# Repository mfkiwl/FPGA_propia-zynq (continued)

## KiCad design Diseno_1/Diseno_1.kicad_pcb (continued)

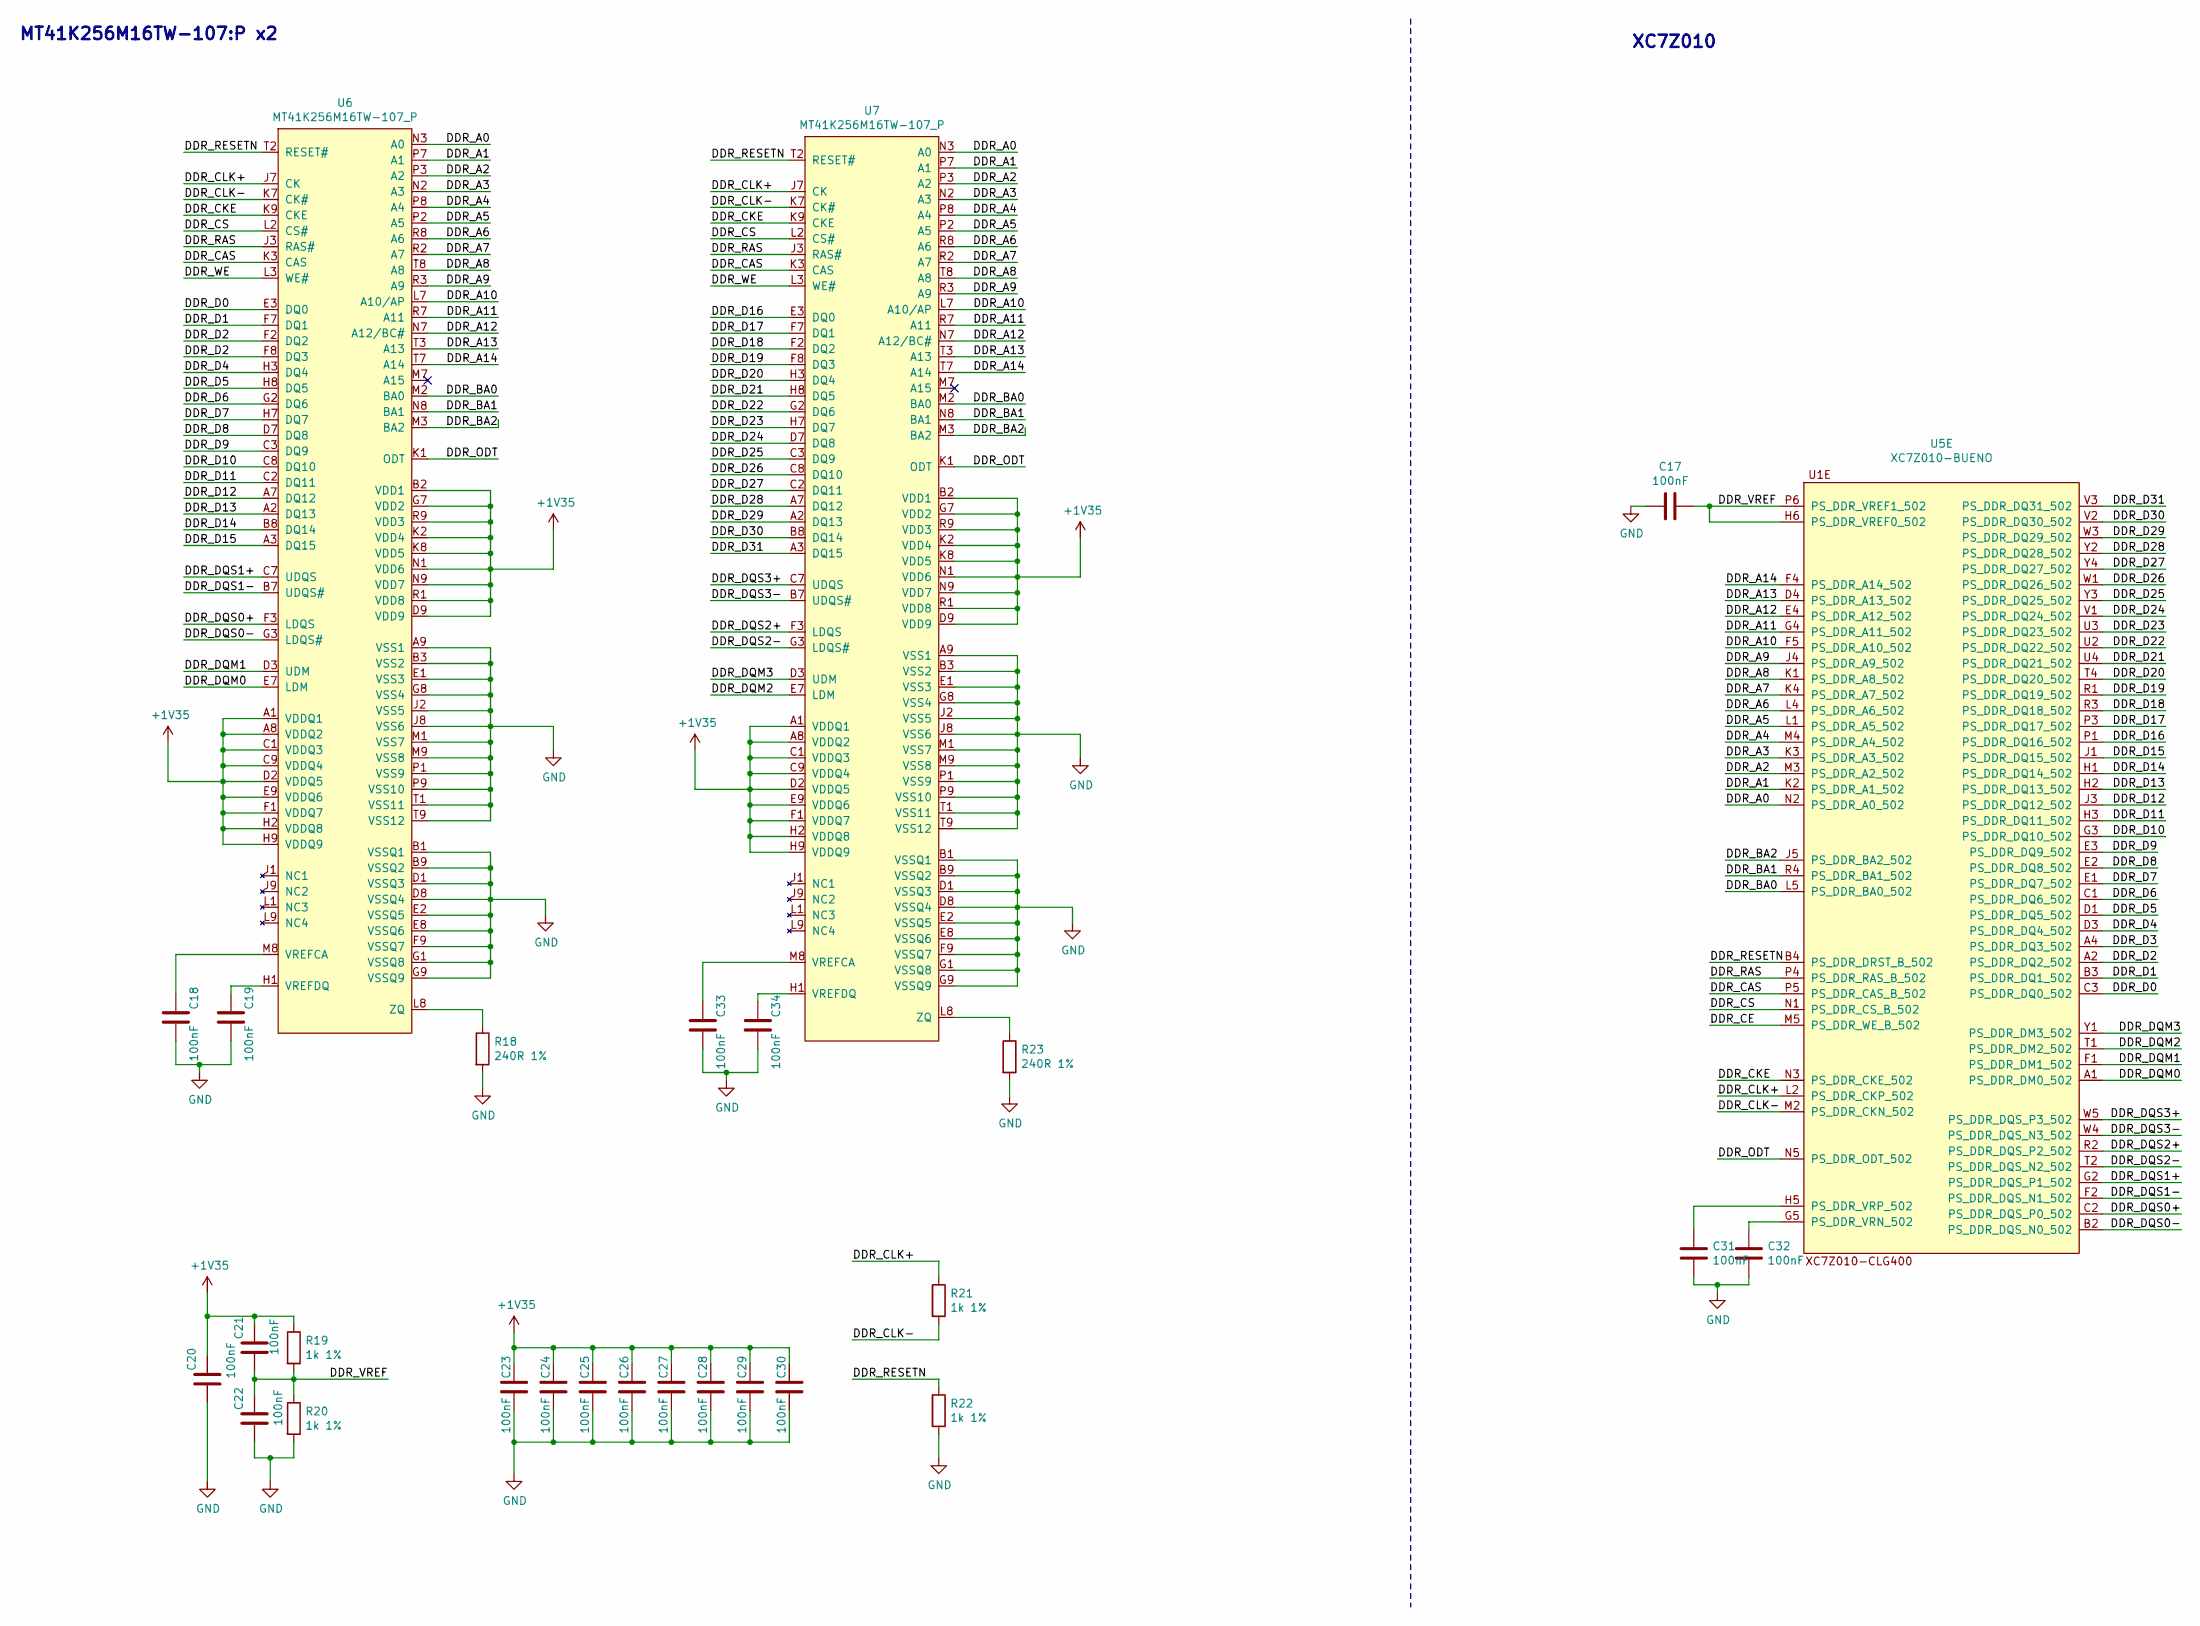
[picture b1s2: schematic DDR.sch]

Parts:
C17, C18, C19, C20, C21, C22, C23, C24, C25, C26, C27, C28, C29, C30, C31, C32, C33, C34: 100nF; C_0805_2012Metric
R18, R23: 240R 1%; R_0805_2012Metric
R19, R20, R21, R22: 1k 1%; R_0805_2012Metric
U5: XC7Z010-BUENO; BGA-400_20x20_17.0x17.0mm
U6, U7: MT41K256M16TW-107_P; BGA-144_9x16_8.0x14.0mm

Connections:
+1V35: C20.1, C21.1, C23.1, C24.1, C25.1, C26.1, C27.1, C28.1, C29.1, C30.1, R19.1, U6.A1 (VDDQ1), U6.A8 (VDDQ2), U6.B2 (VDD1), U6.C1 (VDDQ3), U6.C9 (VDDQ4), U6.D2 (VDDQ5), U6.D9 (VDD9), U6.E9 (VDDQ6), U6.F1 (VDDQ7), U6.G7 (VDD2), U6.H2 (VDDQ8), U6.H9 (VDDQ9), U6.K2 (VDD4), U6.K8 (VDD5), U6.N1 (VDD6), U6.N9 (VDD7), U6.R1 (VDD8), U6.R9 (VDD3), U7.A1 (VDDQ1), U7.A8 (VDDQ2), U7.B2 (VDD1), U7.C1 (VDDQ3), U7.C9 (VDDQ4), U7.D2 (VDDQ5), U7.D9 (VDD9), U7.E9 (VDDQ6), U7.F1 (VDDQ7), U7.G7 (VDD2), U7.H2 (VDDQ8), U7.H9 (VDDQ9), U7.K2 (VDD4), U7.K8 (VDD5), U7.N1 (VDD6), U7.N9 (VDD7), U7.R1 (VDD8), U7.R9 (VDD3); also elsewhere on the board
/Entradas y Salidas/BANK34_N17: U5.N17 (IO_L23P_T3_34); also elsewhere on the board
/Entradas y Salidas/BANK34_N18: U5.N18 (IO_L13P_T2_MRCC_34); also elsewhere on the board
/Entradas y Salidas/BANK34_N20: U5.N20 (IO_L14P_T2_SRCC_34); also elsewhere on the board
/Entradas y Salidas/BANK34_P14: U5.P14 (IO_L6P_T0_34); also elsewhere on the board
/Entradas y Salidas/BANK34_P15: U5.P15 (IO_L24P_T3_34); also elsewhere on the board
/Entradas y Salidas/BANK34_P16: U5.P16 (IO_L24N_T3_34); also elsewhere on the board
/Entradas y Salidas/BANK34_P18: U5.P18 (IO_L23N_T3_34); also elsewhere on the board
/Entradas y Salidas/BANK34_P19: U5.P19 (IO_L13N_T2_MRCC_34); also elsewhere on the board
/Entradas y Salidas/BANK34_P20: U5.P20 (IO_L14N_T2_SRCC_34); also elsewhere on the board
/Entradas y Salidas/BANK34_R14: U5.R14 (IO_L6N_T0_VREF_34); also elsewhere on the board
/Entradas y Salidas/BANK34_R16: U5.R16 (IO_L19P_T3_34); also elsewhere on the board
/Entradas y Salidas/BANK34_R17: U5.R17 (IO_L19N_T3_VREF_34); also elsewhere on the board
/Entradas y Salidas/BANK34_R18: U5.R18 (IO_L20N_T3_34); also elsewhere on the board
/Entradas y Salidas/BANK34_R19: U5.R19 (IO_0_34); also elsewhere on the board
/Entradas y Salidas/BANK34_T10: U5.T10 (IO_L1N_0_34); also elsewhere on the board
/Entradas y Salidas/BANK34_T11: U5.T11 (IO_L1P_T0_34); also elsewhere on the board
/Entradas y Salidas/BANK34_T12: U5.T12 (IO_L2P_T0_34); also elsewhere on the board
/Entradas y Salidas/BANK34_T14: U5.T14 (IO_l5P_T0_34); also elsewhere on the board
/Entradas y Salidas/BANK34_T15: U5.T15 (IO_L5N_T0_34); also elsewhere on the board
/Entradas y Salidas/BANK34_T16: U5.T16 (IO_L9P_T1_DQS_34); also elsewhere on the board
/Entradas y Salidas/BANK34_T17: U5.T17 (IO_L20P_T3_34); also elsewhere on the board
/Entradas y Salidas/BANK34_T19: U5.T19 (IO_25_34); also elsewhere on the board
/Entradas y Salidas/BANK34_T20: U5.T20 (IO_L15P_T2_DQS_34); also elsewhere on the board
/Entradas y Salidas/BANK34_U12: U5.U12 (IO_L2N_T0_34); also elsewhere on the board
/Entradas y Salidas/BANK34_U14: U5.U14 (IO_L11P_T1_SRCC_34); also elsewhere on the board
/Entradas y Salidas/BANK34_U15: U5.U15 (IO_L11N_T1_SRCC_34); also elsewhere on the board
/Entradas y Salidas/BANK34_U17: U5.U17 (IO_L9N_T1_DQS_34); also elsewhere on the board
/Entradas y Salidas/BANK34_U18: U5.U18 (IO_L12P_T1_MRCC_34); also elsewhere on the board
/Entradas y Salidas/BANK34_U19: U5.U19 (IO_L12N_T1_MRCC_34); also elsewhere on the board
/Entradas y Salidas/BANK34_U20: U5.U20 (IO_L5N_T2_DQS_34); also elsewhere on the board
/Entradas y Salidas/BANK34_V12: U5.V12 (IO_L4P_T0_34); also elsewhere on the board
/Entradas y Salidas/BANK34_V13: U5.V13 (IO_L3N_T0_DQS_34); also elsewhere on the board
/Entradas y Salidas/BANK34_V15: U5.V15 (IO_L10P_T1_34); also elsewhere on the board
/Entradas y Salidas/BANK34_V16: U5.V16 (IO_L18P_T2_34); also elsewhere on the board
/Entradas y Salidas/BANK34_V17: U5.V17 (IO_L21P_T3_VREF_34); also elsewhere on the board
/Entradas y Salidas/BANK34_V18: U5.V18 (IO_L21N_T3_DQS_34); also elsewhere on the board
/Entradas y Salidas/BANK34_V20: U5.V20 (IO_L6P_T2_34); also elsewhere on the board
/Entradas y Salidas/BANK34_W13: U5.W13 (IO_L4N_T0_34); also elsewhere on the board
/Entradas y Salidas/BANK34_W14: U5.W14 (IO_L8P_T1_34); also elsewhere on the board
/Entradas y Salidas/BANK34_W15: U5.W15 (IO_L10N_T1_34); also elsewhere on the board
/Entradas y Salidas/BANK34_W16: U5.W16 (IO_L18N_T2_34); also elsewhere on the board
/Entradas y Salidas/BANK34_W18: U5.W18 (IO_L22P_T3_34); also elsewhere on the board
/Entradas y Salidas/BANK34_W19: U5.W19 (IO_L22N_T3_34); also elsewhere on the board
/Entradas y Salidas/BANK34_W20: U5.W20 (IO_L6N_T2_34); also elsewhere on the board
/Entradas y Salidas/BANK34_Y14: U5.Y14 (IO_L8N_T1_34); also elsewhere on the board
/Entradas y Salidas/BANK34_Y16: U5.Y16 (IO_L7P_T1_34); also elsewhere on the board
/Entradas y Salidas/BANK34_Y17: U5.Y17 (IO_L7N_T1_34); also elsewhere on the board
/Entradas y Salidas/BANK34_Y18: U5.Y18 (IO_L17P_T2_34); also elsewhere on the board
/Entradas y Salidas/BANK34_Y19: U5.Y19 (IO_L17N_T2_34); also elsewhere on the board
/Entradas y Salidas/BANK35_A20: U5.A20 (IO_L2N_T0_AD8N_35); also elsewhere on the board
/Entradas y Salidas/BANK35_B19: U5.B19 (IO_L2P_T0_AD8P_35); also elsewhere on the board
/Entradas y Salidas/BANK35_B20: U5.B20 (IO_L1N_T0_AD0P_35); also elsewhere on the board
/Entradas y Salidas/BANK35_C20: U5.C20 (IO_L1P_T0_AD0P_35); also elsewhere on the board
/Entradas y Salidas/BANK35_D18: U5.D18 (IO_L3N_T0_DQS_AD1N_35); also elsewhere on the board
/Entradas y Salidas/BANK35_D19: U5.D19 (IO_L4P_T0_35); also elsewhere on the board
/Entradas y Salidas/BANK35_D20: U5.D20 (IO_L4N_T0_35); also elsewhere on the board
/Entradas y Salidas/BANK35_E17: U5.E17 (IO_L3P_T0_DQS_AD1P_35); also elsewhere on the board
/Entradas y Salidas/BANK35_E18: U5.E18 (IO_L5P_T0_AD9P_35); also elsewhere on the board
/Entradas y Salidas/BANK35_E19: U5.E19 (IO_L5N_T0_AD9N_35); also elsewhere on the board
/Entradas y Salidas/BANK35_F16: U5.F16 (IO_L6P_T0_35); also elsewhere on the board
/Entradas y Salidas/BANK35_F17: U5.F17 (IO_L6N_T0_VREF_35); also elsewhere on the board
/Entradas y Salidas/BANK35_F19: U5.F19 (IO_L15P_T2_DQS_AD12P_35); also elsewhere on the board
/Entradas y Salidas/BANK35_F20: U5.F20 (IO_L15N_T2_DQS_AD12N_35); also elsewhere on the board
/Entradas y Salidas/BANK35_G14: U5.G14 (IO_0_35); also elsewhere on the board
/Entradas y Salidas/BANK35_G15: U5.G15 (IO_L19N_T3_VREF_35); also elsewhere on the board
/Entradas y Salidas/BANK35_G17: U5.G17 (IO_L16P_T2_35); also elsewhere on the board
/Entradas y Salidas/BANK35_G18: U5.G18 (IO_L16N_T2_35); also elsewhere on the board
/Entradas y Salidas/BANK35_G19: U5.G19 (IO_L18P_T2_AD13P_35); also elsewhere on the board
/Entradas y Salidas/BANK35_G20: U5.G20 (IO_L18N_T2_AD13N_35); also elsewhere on the board
/Entradas y Salidas/BANK35_H15: U5.H15 (IO_L19P_T3_35); also elsewhere on the board
/Entradas y Salidas/BANK35_H16: U5.H16 (IO_L13P_T2_MRCC_35); also elsewhere on the board
/Entradas y Salidas/BANK35_H17: U5.H17 (IO_L13N_T2_MRCC_35); also elsewhere on the board
/Entradas y Salidas/BANK35_H18: U5.H18 (IO_L14N_T2_AD4N_SRCC_35); also elsewhere on the board
/Entradas y Salidas/BANK35_H20: U5.H20 (IO_L17N_T2_AD5N_35); also elsewhere on the board
/Entradas y Salidas/BANK35_J14: U5.J14 (IO_L20N_T3_AD6N_35); also elsewhere on the board
/Entradas y Salidas/BANK35_J15: U5.J15 (IO_25_35); also elsewhere on the board
/Entradas y Salidas/BANK35_J16: U5.J16 (IO_L24N_T3_AD15N_35); also elsewhere on the board
/Entradas y Salidas/BANK35_J18: U5.J18 (IO_L14P_T2_AD4P_SRCC_35); also elsewhere on the board
/Entradas y Salidas/BANK35_J19: U5.J19 (IO_L10N_AD11N_35); also elsewhere on the board
/Entradas y Salidas/BANK35_J20: U5.J20 (IO_L17P_T2_AD5P_35); also elsewhere on the board
/Entradas y Salidas/BANK35_K14: U5.K14 (IO_L20P_T3_AD6P_35); also elsewhere on the board
/Entradas y Salidas/BANK35_K16: U5.K16 (IO_L24P_T3_AD15P_35); also elsewhere on the board
/Entradas y Salidas/BANK35_K17: U5.K17 (IO_L12P_T1_MRCC_35); also elsewhere on the board
/Entradas y Salidas/BANK35_K18: U5.K18 (IO_L12N_T1_MRCC_35); also elsewhere on the board
/Entradas y Salidas/BANK35_K19: U5.K19 (IO_L10P_T1_AD11P_35); also elsewhere on the board
/Entradas y Salidas/BANK35_L14: U5.L14 (IO_L22P_T3_AD7P_35); also elsewhere on the board
/Entradas y Salidas/BANK35_L15: U5.L15 (IO_L22N_T3_AD7N_35); also elsewhere on the board
/Entradas y Salidas/BANK35_L16: U5.L16 (IO_L11P_T1_SRCC_35); also elsewhere on the board
/Entradas y Salidas/BANK35_L17: U5.L17 (IO_L11N_T1_SRCC_35); also elsewhere on the board
/Entradas y Salidas/BANK35_L19: U5.L19 (IO_L9P_T1_DQS_AD3P_35); also elsewhere on the board
/Entradas y Salidas/BANK35_L20: U5.L20 (IO_L9N_T1_DQS_AD3N_35); also elsewhere on the board
/Entradas y Salidas/BANK35_M14: U5.M14 (IO_L23P_T3_35); also elsewhere on the board
/Entradas y Salidas/BANK35_M15: U5.M15 (IO_L23N_T3_35); also elsewhere on the board
/Entradas y Salidas/BANK35_M17: U5.M17 (IO_L8P_T1_AD10P_35); also elsewhere on the board
/Entradas y Salidas/BANK35_M18: U5.M18 (IO_L8N_T1_AD10N_35); also elsewhere on the board
/Entradas y Salidas/BANK35_M19: U5.M19 (IO_L7P_T1_AD2P_35); also elsewhere on the board
/Entradas y Salidas/BANK35_M20: U5.M20 (IO_L7N_T1_AD2N_35); also elsewhere on the board
/Entradas y Salidas/BANK35_N15: U5.N15 (IO_L21P_T3_DQS_AD14P_35); also elsewhere on the board
/Entradas y Salidas/BANK35_N16: U5.N16 (IO_L21N_T3_DQS_AD14N_35); also elsewhere on the board
/Memoria RAM/DDR_A0: U5.N2 (PS_DDR_A0_502), U6.N3 (A0), U7.N3 (A0)
/Memoria RAM/DDR_A1: U5.K2 (PS_DDR_A1_502), U6.P7 (A1), U7.P7 (A1)
/Memoria RAM/DDR_A2: U5.M3 (PS_DDR_A2_502), U6.P3 (A2), U7.P3 (A2)
/Memoria RAM/DDR_A3: U5.K3 (PS_DDR_A3_502), U6.N2 (A3), U7.N2 (A3)
/Memoria RAM/DDR_A4: U5.M4 (PS_DDR_A4_502), U6.P8 (A4), U7.P8 (A4)
/Memoria RAM/DDR_A5: U5.L1 (PS_DDR_A5_502), U6.P2 (A5), U7.P2 (A5)
/Memoria RAM/DDR_A6: U5.L4 (PS_DDR_A6_502), U6.R8 (A6), U7.R8 (A6)
/Memoria RAM/DDR_A7: U5.K4 (PS_DDR_A7_502), U6.R2 (A7), U7.R2 (A7)
/Memoria RAM/DDR_A8: U5.K1 (PS_DDR_A8_502), U6.T8 (A8), U7.T8 (A8)
/Memoria RAM/DDR_A9: U5.J4 (PS_DDR_A9_502), U6.R3 (A9), U7.R3 (A9)
/Memoria RAM/DDR_A10: U5.F5 (PS_DDR_A10_502), U6.L7 (A10/AP), U7.L7 (A10/AP)
/Memoria RAM/DDR_A11: U5.G4 (PS_DDR_A11_502), U6.R7 (A11), U7.R7 (A11)
/Memoria RAM/DDR_A12: U5.E4 (PS_DDR_A12_502), U6.N7 (A12/BC#), U7.N7 (A12/BC#)
/Memoria RAM/DDR_A13: U5.D4 (PS_DDR_A13_502), U6.T3 (A13), U7.T3 (A13)
/Memoria RAM/DDR_A14: U5.F4 (PS_DDR_A14_502), U6.T7 (A14), U7.T7 (A14)
/Memoria RAM/DDR_BA0: U5.L5 (PS_DDR_BA0_502), U6.M2 (BA0), U7.M2 (BA0)
/Memoria RAM/DDR_BA1: U5.R4 (PS_DDR_BA1_502), U6.N8 (BA1), U7.N8 (BA1)
/Memoria RAM/DDR_BA2: U5.J5 (PS_DDR_BA2_502), U6.M3 (BA2), U7.M3 (BA2)
/Memoria RAM/DDR_CAS: U5.P5 (PS_DDR_CAS_B_502), U6.K3 (CAS), U7.K3 (CAS)
/Memoria RAM/DDR_CKE: U5.N3 (PS_DDR_CKE_502), U6.K9 (CKE), U7.K9 (CKE)
/Memoria RAM/DDR_CLK+: R21.1, U5.L2 (PS_DDR_CKP_502), U6.J7 (CK), U7.J7 (CK)
/Memoria RAM/DDR_CLK-: R21.2, U5.M2 (PS_DDR_CKN_502), U6.K7 (CK#), U7.K7 (CK#)
/Memoria RAM/DDR_CS: U5.N1 (PS_DDR_CS_B_502), U6.L2 (CS#), U7.L2 (CS#)
/Memoria RAM/DDR_D0: U5.C3 (PS_DDR_DQ0_502), U6.E3 (DQ0)
/Memoria RAM/DDR_D1: U5.B3 (PS_DDR_DQ1_502), U6.F7 (DQ1)
/Memoria RAM/DDR_D2: U5.A2 (PS_DDR_DQ2_502), U6.F2 (DQ2), U6.F8 (DQ3)
/Memoria RAM/DDR_D4: U5.D3 (PS_DDR_DQ4_502), U6.H3 (DQ4)
/Memoria RAM/DDR_D5: U5.D1 (PS_DDR_DQ5_502), U6.H8 (DQ5)
/Memoria RAM/DDR_D6: U5.C1 (PS_DDR_DQ6_502), U6.G2 (DQ6)
/Memoria RAM/DDR_D7: U5.E1 (PS_DDR_DQ7_502), U6.H7 (DQ7)
/Memoria RAM/DDR_D8: U5.E2 (PS_DDR_DQ8_502), U6.D7 (DQ8)
/Memoria RAM/DDR_D9: U5.E3 (PS_DDR_DQ9_502), U6.C3 (DQ9)
/Memoria RAM/DDR_D10: U5.G3 (PS_DDR_DQ10_502), U6.C8 (DQ10)
/Memoria RAM/DDR_D11: U5.H3 (PS_DDR_DQ11_502), U6.C2 (DQ11)
/Memoria RAM/DDR_D12: U5.J3 (PS_DDR_DQ12_502), U6.A7 (DQ12)
/Memoria RAM/DDR_D13: U5.H2 (PS_DDR_DQ13_502), U6.A2 (DQ13)
/Memoria RAM/DDR_D14: U5.H1 (PS_DDR_DQ14_502), U6.B8 (DQ14)
/Memoria RAM/DDR_D15: U5.J1 (PS_DDR_DQ15_502), U6.A3 (DQ15)
/Memoria RAM/DDR_D16: U5.P1 (PS_DDR_DQ16_502), U7.E3 (DQ0)
/Memoria RAM/DDR_D17: U5.P3 (PS_DDR_DQ17_502), U7.F7 (DQ1)
/Memoria RAM/DDR_D18: U5.R3 (PS_DDR_DQ18_502), U7.F2 (DQ2)
/Memoria RAM/DDR_D19: U5.R1 (PS_DDR_DQ19_502), U7.F8 (DQ3)
/Memoria RAM/DDR_D20: U5.T4 (PS_DDR_DQ20_502), U7.H3 (DQ4)
/Memoria RAM/DDR_D21: U5.U4 (PS_DDR_DQ21_502), U7.H8 (DQ5)
/Memoria RAM/DDR_D22: U5.U2 (PS_DDR_DQ22_502), U7.G2 (DQ6)
/Memoria RAM/DDR_D23: U5.U3 (PS_DDR_DQ23_502), U7.H7 (DQ7)
/Memoria RAM/DDR_D24: U5.V1 (PS_DDR_DQ24_502), U7.D7 (DQ8)
/Memoria RAM/DDR_D25: U5.Y3 (PS_DDR_DQ25_502), U7.C3 (DQ9)
/Memoria RAM/DDR_D26: U5.W1 (PS_DDR_DQ26_502), U7.C8 (DQ10)
/Memoria RAM/DDR_D27: U5.Y4 (PS_DDR_DQ27_502), U7.C2 (DQ11)
/Memoria RAM/DDR_D28: U5.Y2 (PS_DDR_DQ28_502), U7.A7 (DQ12)
/Memoria RAM/DDR_D29: U5.W3 (PS_DDR_DQ29_502), U7.A2 (DQ13)
/Memoria RAM/DDR_D30: U5.V2 (PS_DDR_DQ30_502), U7.B8 (DQ14)
/Memoria RAM/DDR_D31: U5.V3 (PS_DDR_DQ31_502), U7.A3 (DQ15)
/Memoria RAM/DDR_DQM0: U5.A1 (PS_DDR_DM0_502), U6.E7 (LDM)
/Memoria RAM/DDR_DQM1: U5.F1 (PS_DDR_DM1_502), U6.D3 (UDM)
/Memoria RAM/DDR_DQM2: U5.T1 (PS_DDR_DM2_502), U7.E7 (LDM)
/Memoria RAM/DDR_DQM3: U5.Y1 (PS_DDR_DM3_502), U7.D3 (UDM)
/Memoria RAM/DDR_DQS0+: U5.C2 (PS_DDR_DQS_P0_502), U6.F3 (LDQS)
/Memoria RAM/DDR_DQS0-: U5.B2 (PS_DDR_DQS_N0_502), U6.G3 (LDQS#)
/Memoria RAM/DDR_DQS1+: U5.G2 (PS_DDR_DQS_P1_502), U6.C7 (UDQS)
/Memoria RAM/DDR_DQS1-: U5.F2 (PS_DDR_DQS_N1_502), U6.B7 (UDQS#)
/Memoria RAM/DDR_DQS2+: U5.R2 (PS_DDR_DQS_P2_502), U7.F3 (LDQS)
/Memoria RAM/DDR_DQS2-: U5.T2 (PS_DDR_DQS_N2_502), U7.G3 (LDQS#)
/Memoria RAM/DDR_DQS3+: U5.W5 (PS_DDR_DQS_P3_502), U7.C7 (UDQS)
/Memoria RAM/DDR_DQS3-: U5.W4 (PS_DDR_DQS_N3_502), U7.B7 (UDQS#)
/Memoria RAM/DDR_ODT: U5.N5 (PS_DDR_ODT_502), U6.K1 (ODT), U7.K1 (ODT)
/Memoria RAM/DDR_RAS: U5.P4 (PS_DDR_RAS_B_502), U6.J3 (RAS#), U7.J3 (RAS#)
/Memoria RAM/DDR_RESETN: R22.1, U5.B4 (PS_DDR_DRST_B_502), U6.T2 (RESET#), U7.T2 (RESET#)
/Memoria RAM/DDR_VREF: C17.1, C21.2, C22.1, R19.2, R20.1, U5.H6 (PS_DDR_VREF0_502), U5.P6 (PS_DDR_VREF1_502)
/Memoria RAM/DDR_WE: U6.L3 (WE#), U7.L3 (WE#)
GND: C17.2, C18.2, C19.2, C20.2, C22.2, C23.2, C24.2, C25.2, C26.2, C27.2, C28.2, C29.2, C30.2, C31.2, C32.2, C33.2, C34.2, R18.2, R20.2, R22.2, R23.2, U5.U13 (IO_L3P_T0_DQS_PUDC_B_34), U6.A9 (VSS1), U6.B1 (VSSQ1), U6.B3 (VSS2), U6.B9 (VSSQ2), U6.D1 (VSSQ3), U6.D8 (VSSQ4), U6.E1 (VSS3), U6.E2 (VSSQ5), U6.E8 (VSSQ6), U6.F9 (VSSQ7), U6.G1 (VSSQ8), U6.G8 (VSS4), U6.G9 (VSSQ9), U6.J2 (VSS5), U6.J8 (VSS6), U6.M1 (VSS7), U6.M9 (VSS8), U6.P1 (VSS9), U6.P9 (VSS10), U6.T1 (VSS11), U6.T9 (VSS12), U7.A9 (VSS1), U7.B1 (VSSQ1), U7.B3 (VSS2), U7.B9 (VSSQ2), U7.D1 (VSSQ3), U7.D8 (VSSQ4), U7.E1 (VSS3), U7.E2 (VSSQ5), U7.E8 (VSSQ6), U7.F9 (VSSQ7), U7.G1 (VSSQ8), U7.G8 (VSS4), U7.G9 (VSSQ9), U7.J2 (VSS5), U7.J8 (VSS6), U7.M1 (VSS7), U7.M9 (VSS8), U7.P1 (VSS9), U7.P9 (VSS10), U7.T1 (VSS11), U7.T9 (VSS12); also elsewhere on the board
unnamed: C18.1, U6.M8 (VREFCA)
unnamed: C19.1, U6.H1 (VREFDQ)
unnamed: C31.1, U5.H5 (PS_DDR_VRP_502)
unnamed: C32.1, U5.G5 (PS_DDR_VRN_502)
unnamed: C33.1, U7.M8 (VREFCA)
unnamed: C34.1, U7.H1 (VREFDQ)
unnamed: R18.1, U6.L8 (ZQ)
unnamed: R23.1, U7.L8 (ZQ)

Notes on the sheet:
XC7Z010
MT41K256M16TW-107:P x2
